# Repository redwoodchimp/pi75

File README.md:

75% keyboard that uses a Raspberry Pi Pico

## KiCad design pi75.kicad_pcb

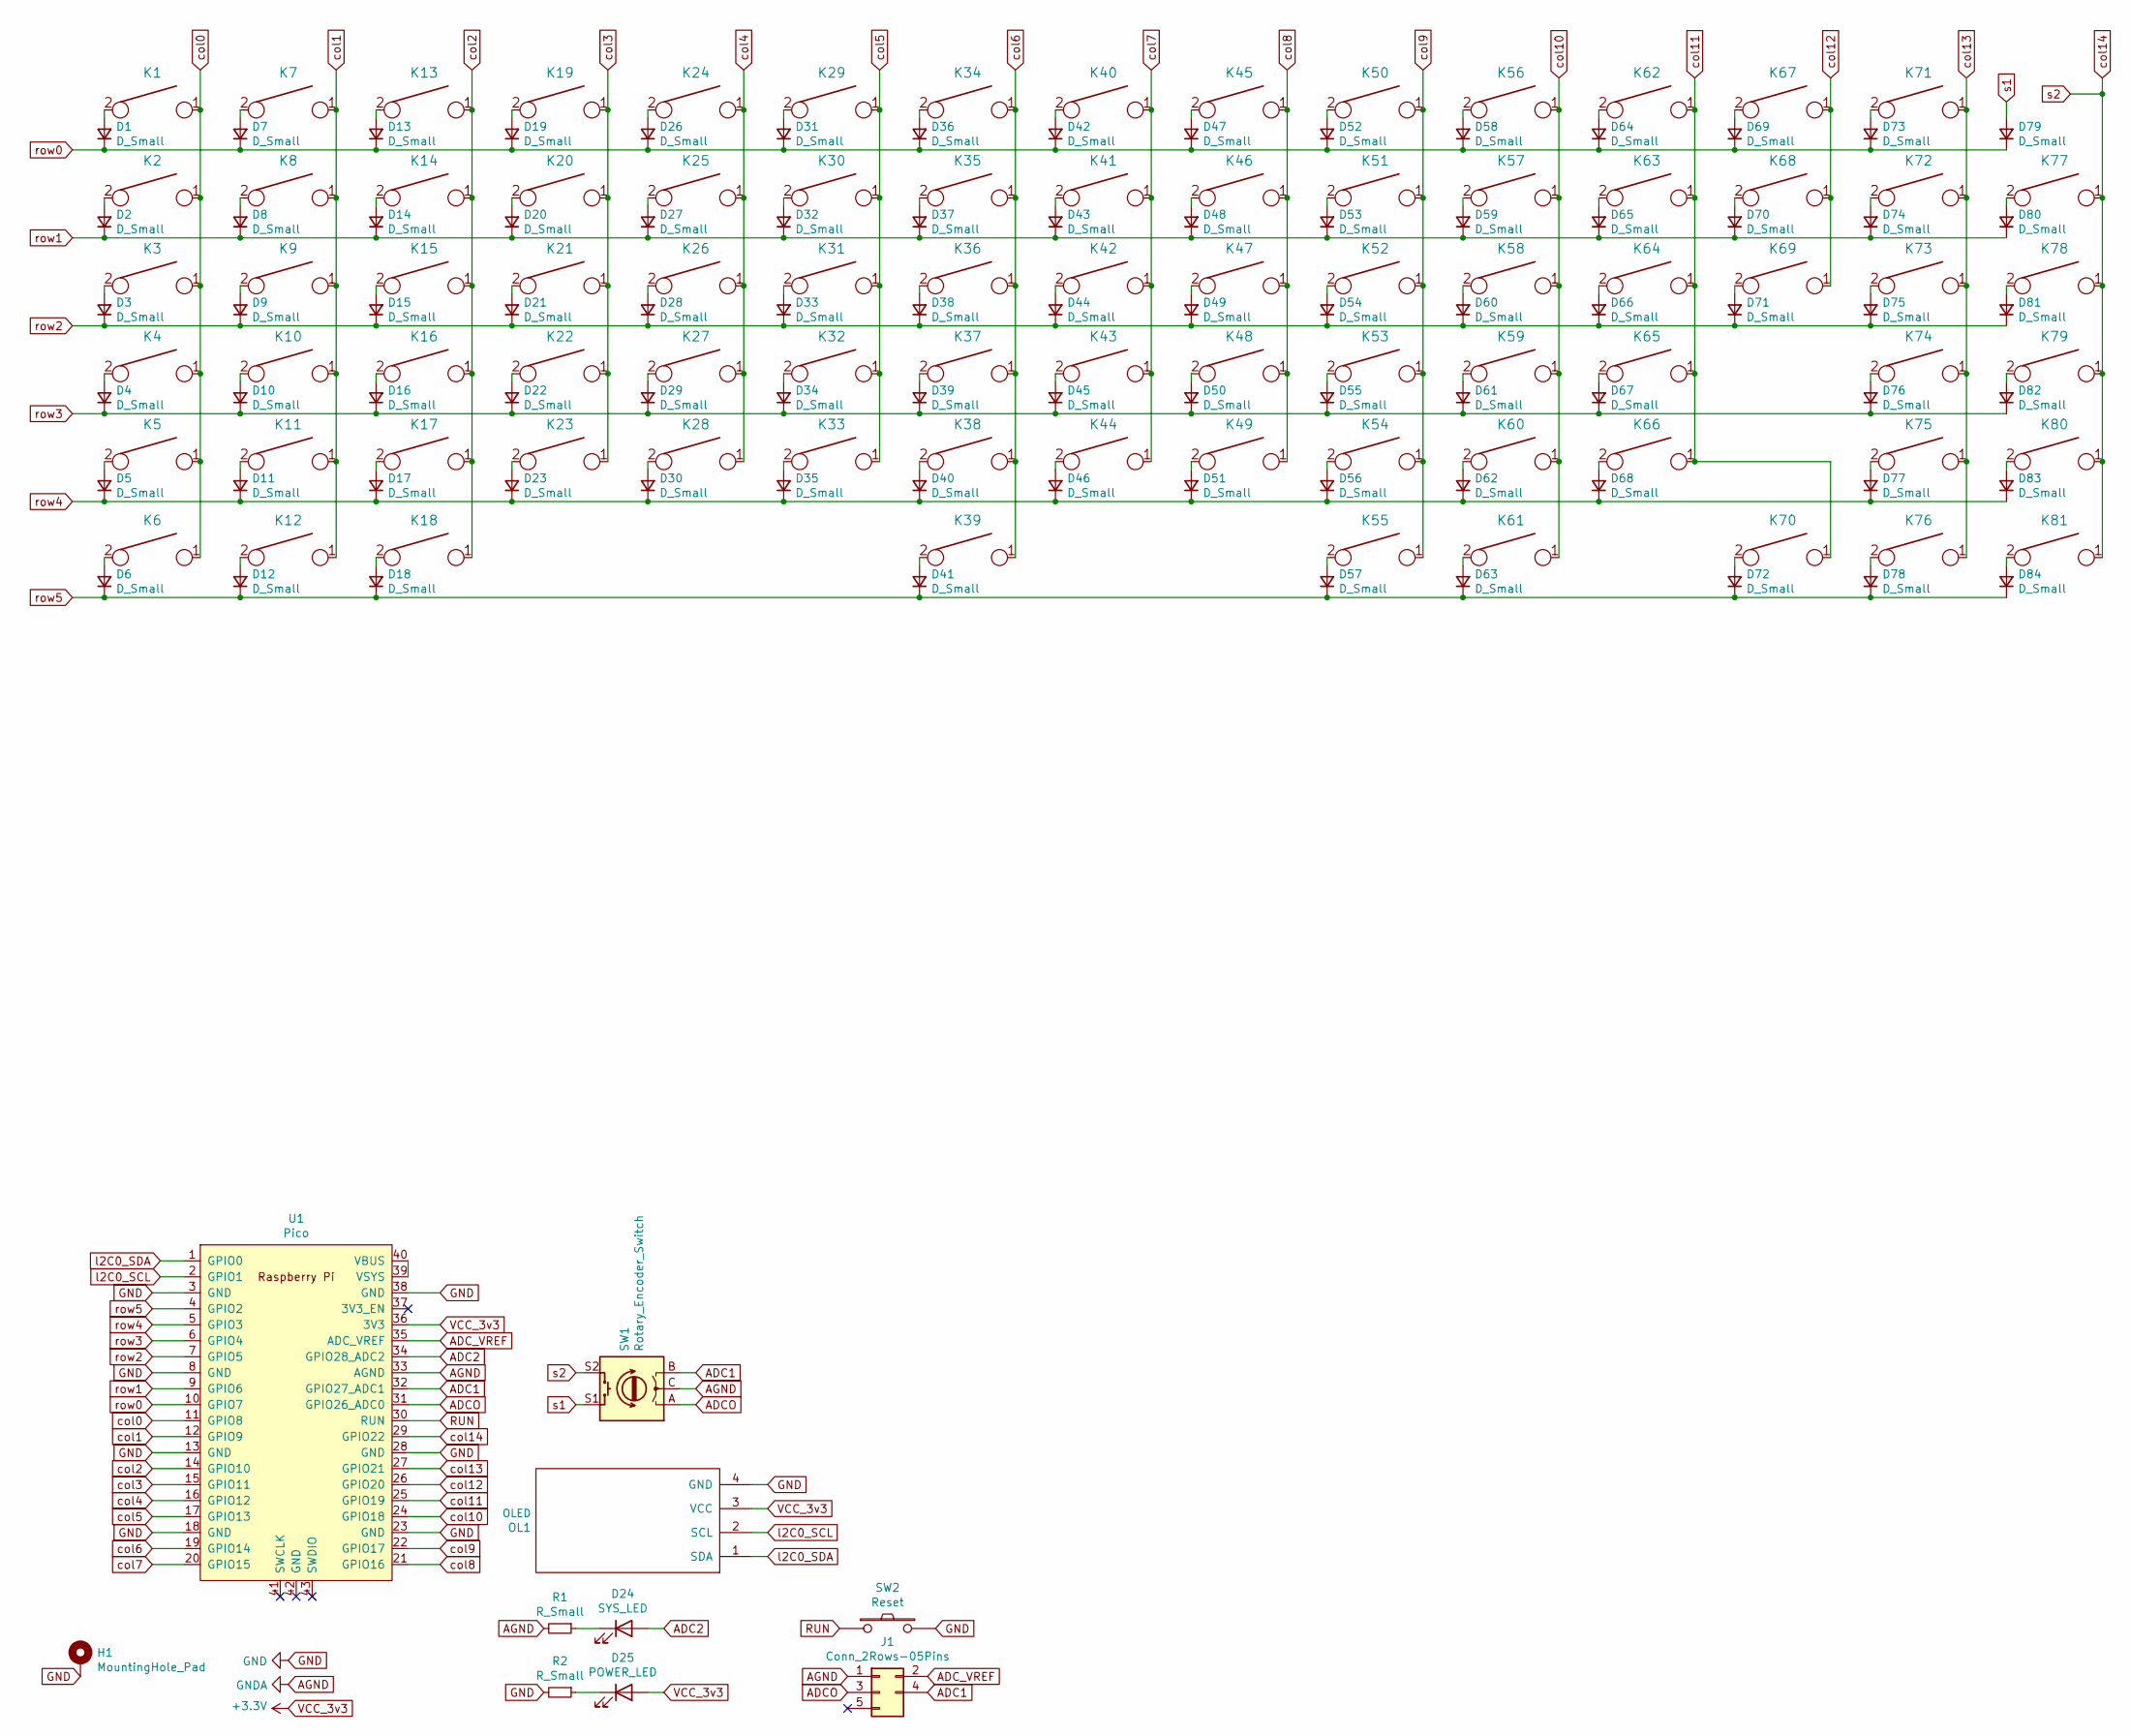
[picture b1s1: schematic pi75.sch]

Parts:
D1, D2, D3, D4, D5, D6, D7, D8, D9, D10, D11, D12, D13, D14, D15, D16, D17, D18, D19, D20, D21, D22, D23, D26, D27, D28, D29, D30, D31, D32, D33, D34, D35, D36, D37, D38, D39, D40, D41, D42, D43, D44, D45, D46, D47, D48, D49, D50, D51, D52, D53, D54, D55, D56, D57, D58, D59, D60, D61, D62, D63, D64, D65, D66, D67, D68, D69, D70, D71, D72, D73, D74, D75, D76, D77, D78, D79, D80, D81, D82, D83, D84: D_Small; D_DO-35_SOD27_P5.08mm_Horizontal
D24: SYS_LED; LED_D3.0mm
D25: POWER_LED; LED_D3.0mm
H1: MountingHole_Pad; MountingHole_2.2mm_M2_Pad
J1: Conn_2Rows-05Pins; oled-mirroed
K1, K2, K7, K8, K9, K10, K11, K13, K14, K15, K16, K17, K19, K20, K21, K22, K23, K24, K25, K26, K27, K28, K29, K30, K31, K32, K33, K34, K35, K36, K37, K38, K40, K41, K42, K43, K44, K45, K46, K47, K48, K49, K50, K51, K52, K53, K54, K56, K57, K58, K59, K60, K62, K63, K64, K65, K67, K68, K69, K70, K71, K75, K76, K77, K78, K79, K80, K81: KEYSW-keyboard_parts; MXOnly-1U-Hotswap
K3, K55, K61, K73: KEYSW-keyboard_parts; MXOnly-1.5U-Hotswap
K4, K66: KEYSW-keyboard_parts; MXOnly-1.75U-Hotswap
K5, K74: KEYSW-keyboard_parts; MXOnly-2.25U-Hotswap-ReversedStabilizers
K6, K12, K18: KEYSW-keyboard_parts; MXOnly-1.25U-Hotswap
K39: KEYSW-keyboard_parts; MXOnly-6.25U-Hotswap-ReversedStabilizers
K72: KEYSW-keyboard_parts; MXOnly-2U-Hotswap-ReversedStabilizers
OL1: OLED; oled-mirroed
R1, R2: R_Small; Resistor-2
SW1: Rotary_Encoder_Switch; RotaryEncoder_Alps_EC11E-Switch_Vertical_H20mm
SW2: Reset; SW_PUSH_6mm
U1: Pico; RPi_Pico_TH

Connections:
ADC1: J1.4, SW1.B, U1.32 (GPIO27_ADC1)
ADC2: D24.2 (A), U1.34 (GPIO28_ADC2)
ADCO: J1.3, SW1.A, U1.31 (GPIO26_ADC0)
ADC_VREF: J1.2, U1.35 (ADC_VREF)
AGND: J1.1, R1.2, SW1.C, U1.33 (AGND)
GND: H1.1, OL1.4 (GND), R2.2, SW2.2, U1.3 (GND), U1.8 (GND), U1.13 (GND), U1.18 (GND), U1.23 (GND), U1.28 (GND), U1.38 (GND)
unnamed: D1.2 (A), K1.2
unnamed: D2.2 (A), K2.2
unnamed: D3.2 (A), K3.2
unnamed: D4.2 (A), K4.2
unnamed: D5.2 (A), K5.2
unnamed: D6.2 (A), K6.2
unnamed: D7.2 (A), K7.2
unnamed: D8.2 (A), K8.2
unnamed: D9.2 (A), K9.2
unnamed: D10.2 (A), K10.2
unnamed: D11.2 (A), K11.2
unnamed: D12.2 (A), K12.2
unnamed: D13.2 (A), K13.2
unnamed: D14.2 (A), K14.2
unnamed: D15.2 (A), K15.2
unnamed: D16.2 (A), K16.2
unnamed: D17.2 (A), K17.2
unnamed: D18.2 (A), K18.2
unnamed: D19.2 (A), K19.2
unnamed: D20.2 (A), K20.2
unnamed: D21.2 (A), K21.2
unnamed: D22.2 (A), K22.2
unnamed: D23.2 (A), K23.2
unnamed: D24.1 (K), R1.1
unnamed: D25.1 (K), R2.1
unnamed: D26.2 (A), K24.2
unnamed: D27.2 (A), K25.2
unnamed: D28.2 (A), K26.2
unnamed: D29.2 (A), K27.2
unnamed: D30.2 (A), K28.2
unnamed: D31.2 (A), K29.2
unnamed: D32.2 (A), K30.2
unnamed: D33.2 (A), K31.2
unnamed: D34.2 (A), K32.2
unnamed: D35.2 (A), K33.2
unnamed: D36.2 (A), K34.2
unnamed: D37.2 (A), K35.2
unnamed: D38.2 (A), K36.2
unnamed: D39.2 (A), K37.2
unnamed: D40.2 (A), K38.2
unnamed: D41.2 (A), K39.2
unnamed: D42.2 (A), K40.2
unnamed: D43.2 (A), K41.2
unnamed: D44.2 (A), K42.2
unnamed: D45.2 (A), K43.2
unnamed: D46.2 (A), K44.2
unnamed: D47.2 (A), K45.2
unnamed: D48.2 (A), K46.2
unnamed: D49.2 (A), K47.2
unnamed: D50.2 (A), K48.2
unnamed: D51.2 (A), K49.2
unnamed: D52.2 (A), K50.2
unnamed: D53.2 (A), K51.2
unnamed: D54.2 (A), K52.2
unnamed: D55.2 (A), K53.2
unnamed: D56.2 (A), K54.2
unnamed: D57.2 (A), K55.2
unnamed: D58.2 (A), K56.2
unnamed: D59.2 (A), K57.2
unnamed: D60.2 (A), K58.2
unnamed: D61.2 (A), K59.2
unnamed: D62.2 (A), K60.2
unnamed: D63.2 (A), K61.2
unnamed: D64.2 (A), K62.2
unnamed: D65.2 (A), K63.2
unnamed: D66.2 (A), K64.2
unnamed: D67.2 (A), K65.2
unnamed: D68.2 (A), K66.2
unnamed: D69.2 (A), K67.2
unnamed: D70.2 (A), K68.2
unnamed: D71.2 (A), K69.2
unnamed: D72.2 (A), K70.2
unnamed: D73.2 (A), K71.2
unnamed: D74.2 (A), K72.2
unnamed: D75.2 (A), K73.2
unnamed: D76.2 (A), K74.2
unnamed: D77.2 (A), K75.2
unnamed: D78.2 (A), K76.2
unnamed: D80.2 (A), K77.2
unnamed: D81.2 (A), K78.2
unnamed: D82.2 (A), K79.2
unnamed: D83.2 (A), K80.2
unnamed: D84.2 (A), K81.2
unnamed: U1.39 (VSYS), U1.40 (VBUS)
RUN: SW2.1, U1.30 (RUN)
VCC_3v3: D25.2 (A), OL1.3 (VCC), U1.36 (3V3)
col0: K1.1, K2.1, K3.1, K4.1, K5.1, K6.1, U1.11 (GPIO8)
col1: K7.1, K8.1, K9.1, K10.1, K11.1, K12.1, U1.12 (GPIO9)
col2: K13.1, K14.1, K15.1, K16.1, K17.1, K18.1, U1.14 (GPIO10)
col3: K19.1, K20.1, K21.1, K22.1, K23.1, U1.15 (GPIO11)
col4: K24.1, K25.1, K26.1, K27.1, K28.1, U1.16 (GPIO12)
col5: K29.1, K30.1, K31.1, K32.1, K33.1, U1.17 (GPIO13)
col6: K34.1, K35.1, K36.1, K37.1, K38.1, K39.1, U1.19 (GPIO14)
col7: K40.1, K41.1, K42.1, K43.1, K44.1, U1.20 (GPIO15)
col8: K45.1, K46.1, K47.1, K48.1, K49.1, U1.21 (GPIO16)
col9: K50.1, K51.1, K52.1, K53.1, K54.1, K55.1, U1.22 (GPIO17)
col10: K56.1, K57.1, K58.1, K59.1, K60.1, K61.1, U1.24 (GPIO18)
col11: K62.1, K63.1, K64.1, K65.1, K66.1, K70.1, U1.25 (GPIO19)
col12: K67.1, K68.1, K69.1, U1.26 (GPIO20)
col13: K71.1, K72.1, K73.1, K74.1, K75.1, K76.1, U1.27 (GPIO21)
col14: K77.1, K78.1, K79.1, K80.1, K81.1, SW1.S2, U1.29 (GPIO22)
l2C0_SCL: OL1.2 (SCL), U1.2 (GPIO1)
l2C0_SDA: OL1.1 (SDA), U1.1 (GPIO0)
row0: D1.1 (K), D7.1 (K), D13.1 (K), D19.1 (K), D26.1 (K), D31.1 (K), D36.1 (K), D42.1 (K), D47.1 (K), D52.1 (K), D58.1 (K), D64.1 (K), D69.1 (K), D73.1 (K), D79.1 (K), U1.10 (GPIO7)
row1: D2.1 (K), D8.1 (K), D14.1 (K), D20.1 (K), D27.1 (K), D32.1 (K), D37.1 (K), D43.1 (K), D48.1 (K), D53.1 (K), D59.1 (K), D65.1 (K), D70.1 (K), D74.1 (K), D80.1 (K), U1.9 (GPIO6)
row2: D3.1 (K), D9.1 (K), D15.1 (K), D21.1 (K), D28.1 (K), D33.1 (K), D38.1 (K), D44.1 (K), D49.1 (K), D54.1 (K), D60.1 (K), D66.1 (K), D71.1 (K), D75.1 (K), D81.1 (K), U1.7 (GPIO5)
row3: D4.1 (K), D10.1 (K), D16.1 (K), D22.1 (K), D29.1 (K), D34.1 (K), D39.1 (K), D45.1 (K), D50.1 (K), D55.1 (K), D61.1 (K), D67.1 (K), D76.1 (K), D82.1 (K), U1.6 (GPIO4)
row4: D5.1 (K), D11.1 (K), D17.1 (K), D23.1 (K), D30.1 (K), D35.1 (K), D40.1 (K), D46.1 (K), D51.1 (K), D56.1 (K), D62.1 (K), D68.1 (K), D77.1 (K), D83.1 (K), U1.5 (GPIO3)
row5: D6.1 (K), D12.1 (K), D18.1 (K), D41.1 (K), D57.1 (K), D63.1 (K), D72.1 (K), D78.1 (K), D84.1 (K), U1.4 (GPIO2)
s1: D79.2 (A), SW1.S1

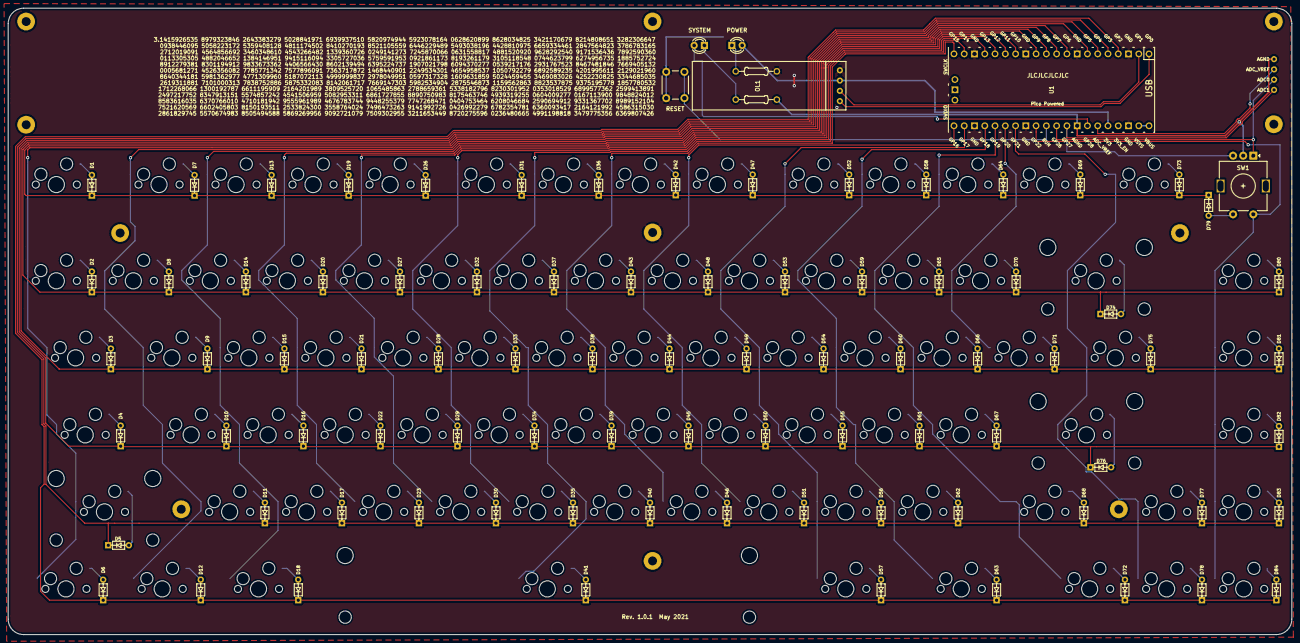
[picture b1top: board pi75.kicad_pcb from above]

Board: 2 copper layers, 317.5 x 154.9 mm, 173 parts (0 on the bottom side), 116 nets.

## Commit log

2021-06-02 init
2021-06-02 Update LICENSE
2021-06-06 Cleaned up schematic
